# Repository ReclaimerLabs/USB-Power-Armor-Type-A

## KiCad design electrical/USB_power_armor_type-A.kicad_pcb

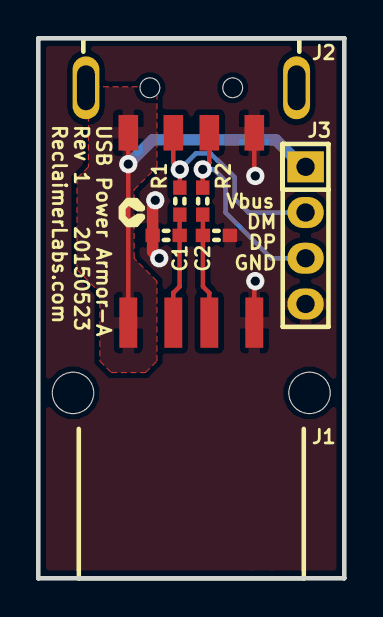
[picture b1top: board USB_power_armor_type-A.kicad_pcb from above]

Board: 2 copper layers, 17.0 x 30.0 mm, 8 parts (0 on the bottom side), 6 nets.

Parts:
 : Reclaimer_Labs_2mm
C1, C2: 1uF; 0603_np
J1: USB_A; USB_A_Female_SMD
J2: USB_A; USB_A_Male_SMD
J3: CONN_01X04; Pin_Header_Straight_1x04
R1, R2: 0R; 0603_np

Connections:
/D+: C2.1, J1.3, R2.2
/D-: C1.1, J1.2, R1.2
/GND: C1.2, C2.2, J1.4, J2.4, J3.4
/Vbus: J1.1, J2.1, J3.1
unnamed: J2.2, J3.2, R1.1
unnamed: J2.3, J3.3, R2.1

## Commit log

2015-06-03 :boom::camel: Added .gitattributes & .gitignore files
2015-06-03 Initial Commit
    USB Power Armor Type-A Rev 1. Charge safely while blocking data.
